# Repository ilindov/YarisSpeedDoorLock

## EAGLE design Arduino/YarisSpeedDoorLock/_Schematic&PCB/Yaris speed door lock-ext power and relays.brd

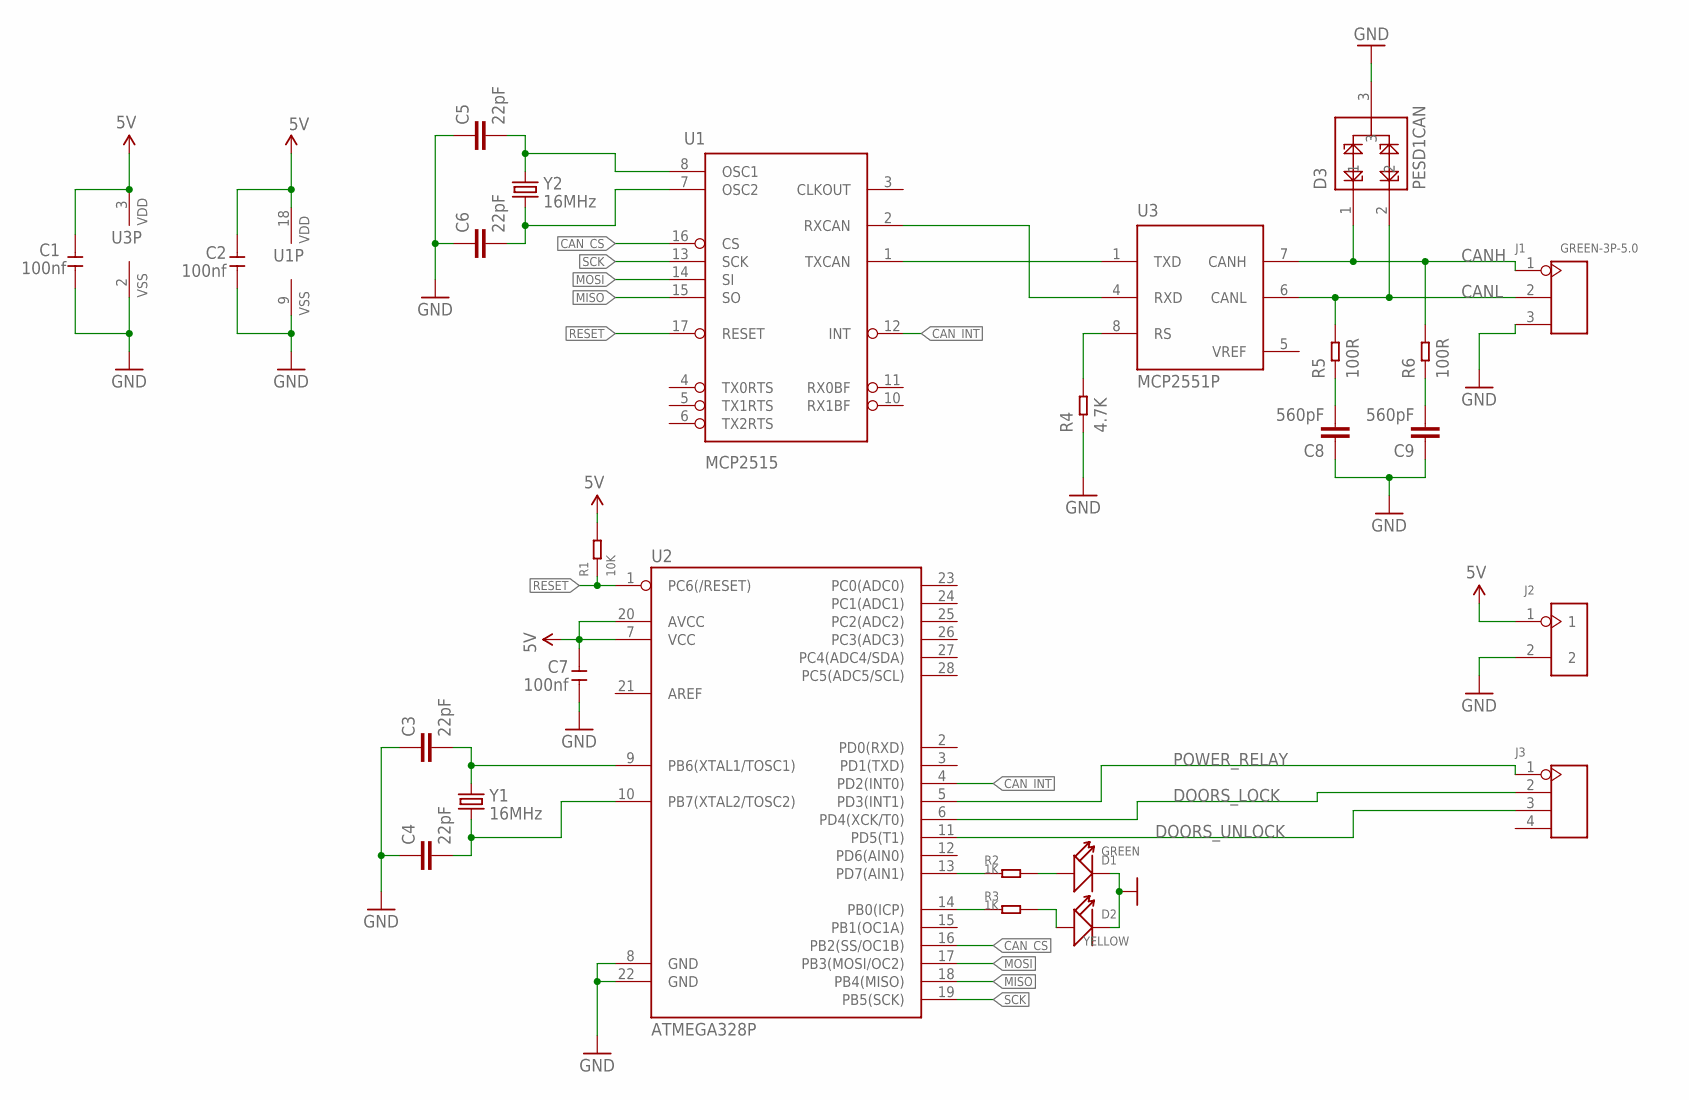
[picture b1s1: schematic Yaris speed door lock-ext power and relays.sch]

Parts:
C1, C2, C7: 100nf; CERAMIC-2.54
C3, C4, C5, C6: 22pF; CAP-PTH-2.54
C8, C9: 560pF; 0603-CAP
D1: GREEN; LED2-2.54-D3.0MM
D2: YELLOW; LED2-2.54-D3.0MM
D3: PESD1CAN; SOT23-3
J1: GREEN-3P-5.0; H3-5.0-15.5X8.0MM
J2: DIP-BLACK-JUMPER; H2-2.54
J3: DIP-BLACK-FEMALE-HEADER-VERT(4P-2.54); H4-2.54
R1: 10K; PR-D2.3XL6.5MM
R2, R3: 1K; PR-D2.3XL6.5MM
R4: 4.7K; PR-D2.3XL6.5MM
R5, R6: 100R; PR-D2.3XL6.5MM
U1: MCP2515; SO-18W
U2: ATMEGA328P; DIP28
U3: MCP2551P; DIL8
Y1, Y2: 16MHz; HC49US

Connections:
5V: C1.2, C2.2, C7.2, J2.1, R1.2, U1.18 (VDD), U2.7 (VCC), U2.20 (AVCC), U3.3 (VDD)
CANH: D3.1, J1.1, R6.2, U3.7 (CANH)
CANL: D3.2, J1.2, R5.2, U3.6 (CANL)
CAN_CS: U1.16 (CS), U2.16 (PB2(SS/OC1B))
CAN_INT: U1.12 (INT), U2.4 (PD2(INT0))
CAN_RXD: U1.2 (RXCAN), U3.4 (RXD)
CAN_TXD: U1.1 (TXCAN), U3.1 (TXD)
DOORS_LOCK: J3.2, U2.6 (PD4(XCK/T0))
DOORS_UNLOCK: J3.3, U2.11 (PD5(T1))
GND: C1.1, C2.1, C3.1, C4.1, C5.1, C6.1, C7.1, C8.1, C9.1, D1.K (-), D2.K (-), D3.3, J1.3, J2.2, R4.1, U1.9 (VSS), U2.8 (GND), U2.22 (GND), U3.2 (VSS)
MISO: U1.15 (SO), U2.18 (PB4(MISO))
MOSI: U1.14 (SI), U2.17 (PB3(MOSI/OC2))
unnamed: C3.2, U2.9 (PB6(XTAL1/TOSC1)), Y1.2
unnamed: C4.2, U2.10 (PB7(XTAL2/TOSC2)), Y1.1
unnamed: C8.2, R5.1
unnamed: C9.2, R6.1
unnamed: R2.1, U2.13 (PD7(AIN1))
unnamed: R4.2, U3.8 (RS)
unnamed: R3.1, U2.14 (PB0(ICP))
unnamed: D1.A (+), R2.2
unnamed: C5.2, U1.8 (OSC1), Y2.2
unnamed: C6.2, U1.7 (OSC2), Y2.1
unnamed: D2.A (+), R3.2
POWER_RELAY: J3.1, U2.5 (PD3(INT1))
RESET: R1.1, U1.17 (RESET), U2.1 (PC6(/RESET))
SCK: U1.13 (SCK), U2.19 (PB5(SCK))
VREF: U3.5 (VREF)

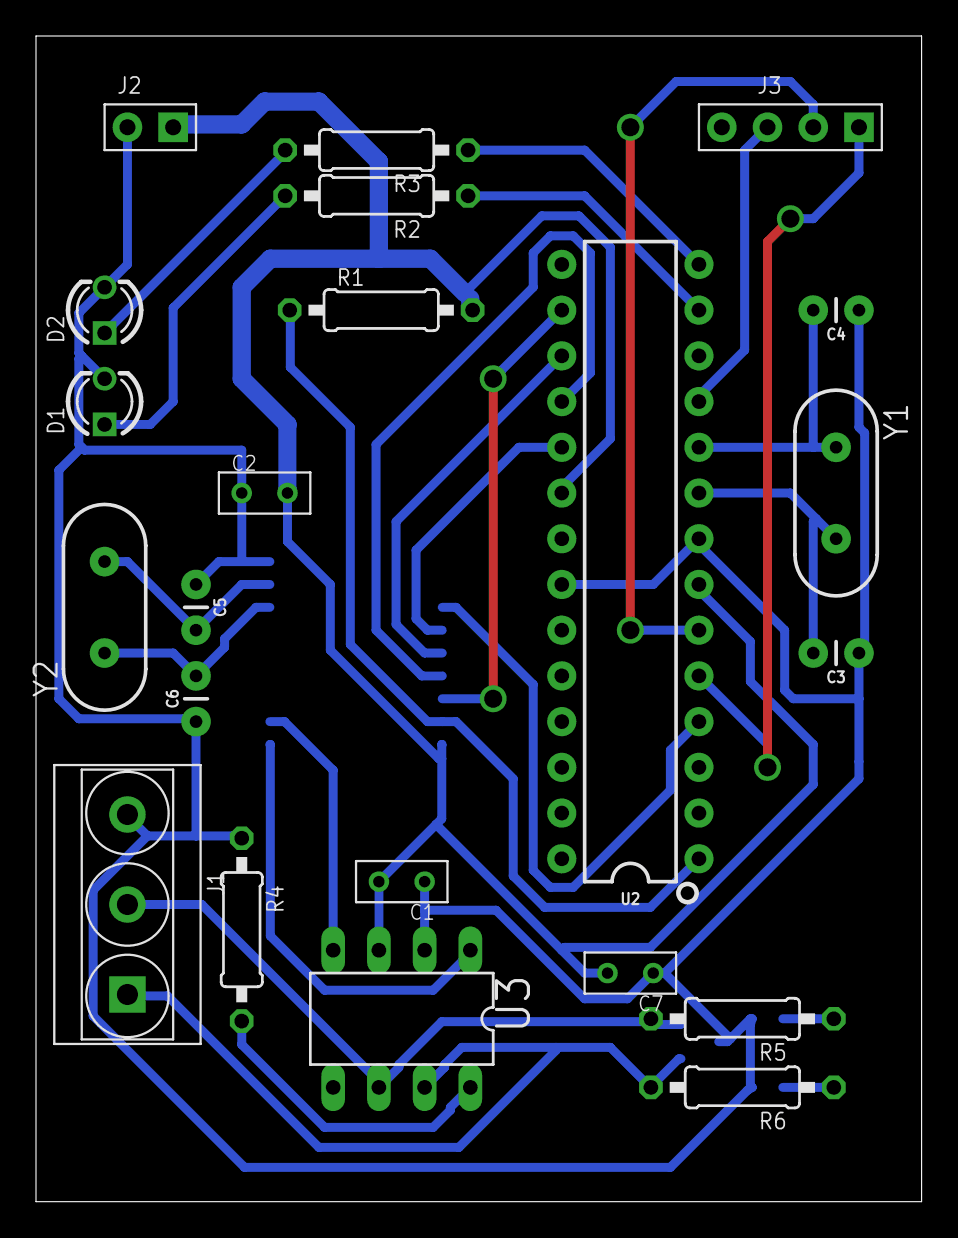
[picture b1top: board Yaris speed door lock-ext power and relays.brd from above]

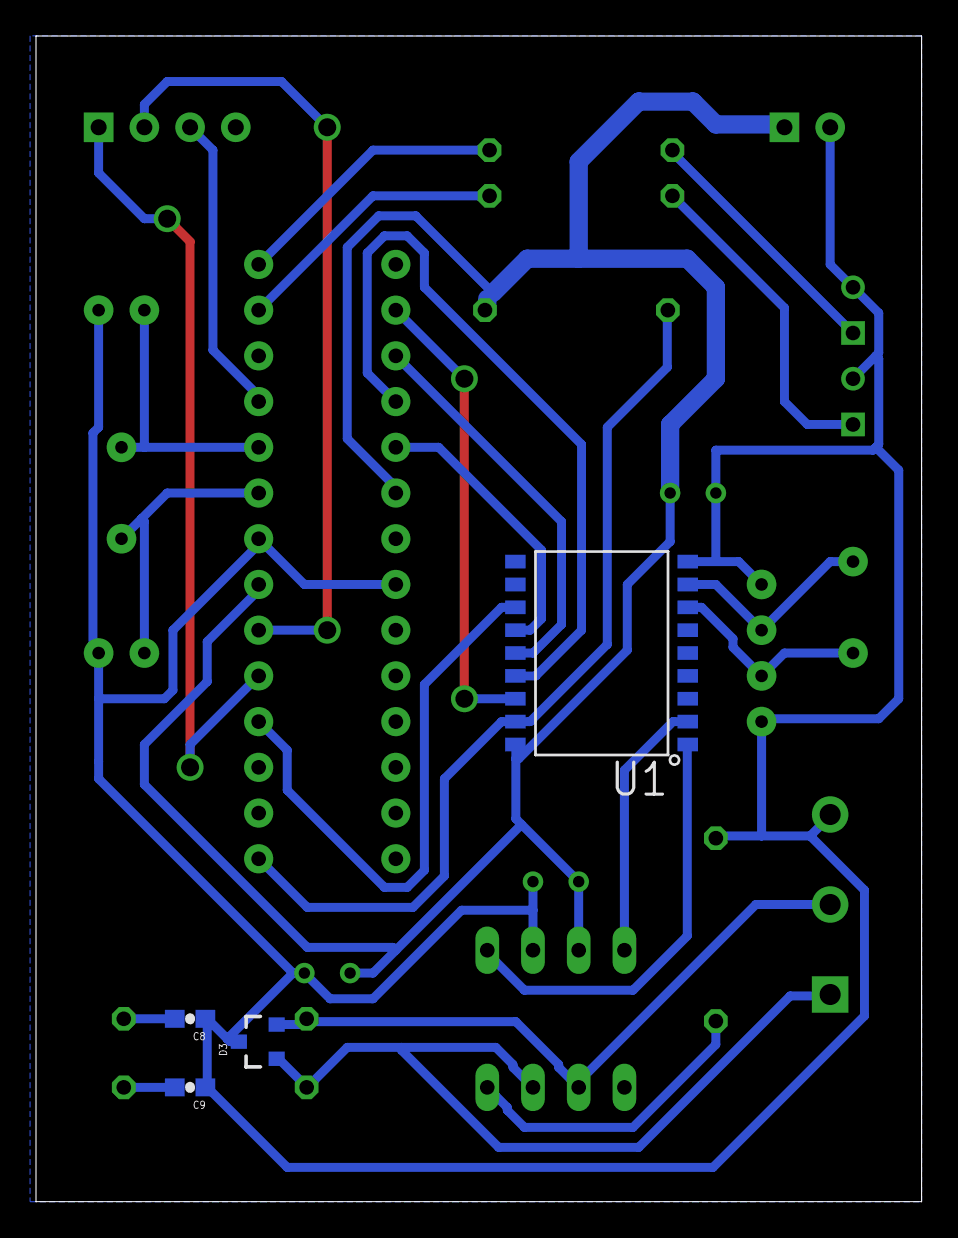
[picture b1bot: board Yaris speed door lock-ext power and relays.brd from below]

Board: 2 copper layers, 49.2 x 64.8 mm, 26 parts (4 on the bottom side), 26 nets.

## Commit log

2019-01-03 Added schematic
2019-01-16 Initial Arduino
2019-01-17 Fixed pinout and changed halt logic

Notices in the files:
parts and their libraries:
SparkFun-Capacitors: Licensing: Creative Commons ShareAlike 4.0 International - https://creativecommons.org/licenses/by-sa/4.0
SparkFun-Aesthetics: Licensing: CC v3.0 Share-Alike You are welcome to use this library for commercial purposes.
